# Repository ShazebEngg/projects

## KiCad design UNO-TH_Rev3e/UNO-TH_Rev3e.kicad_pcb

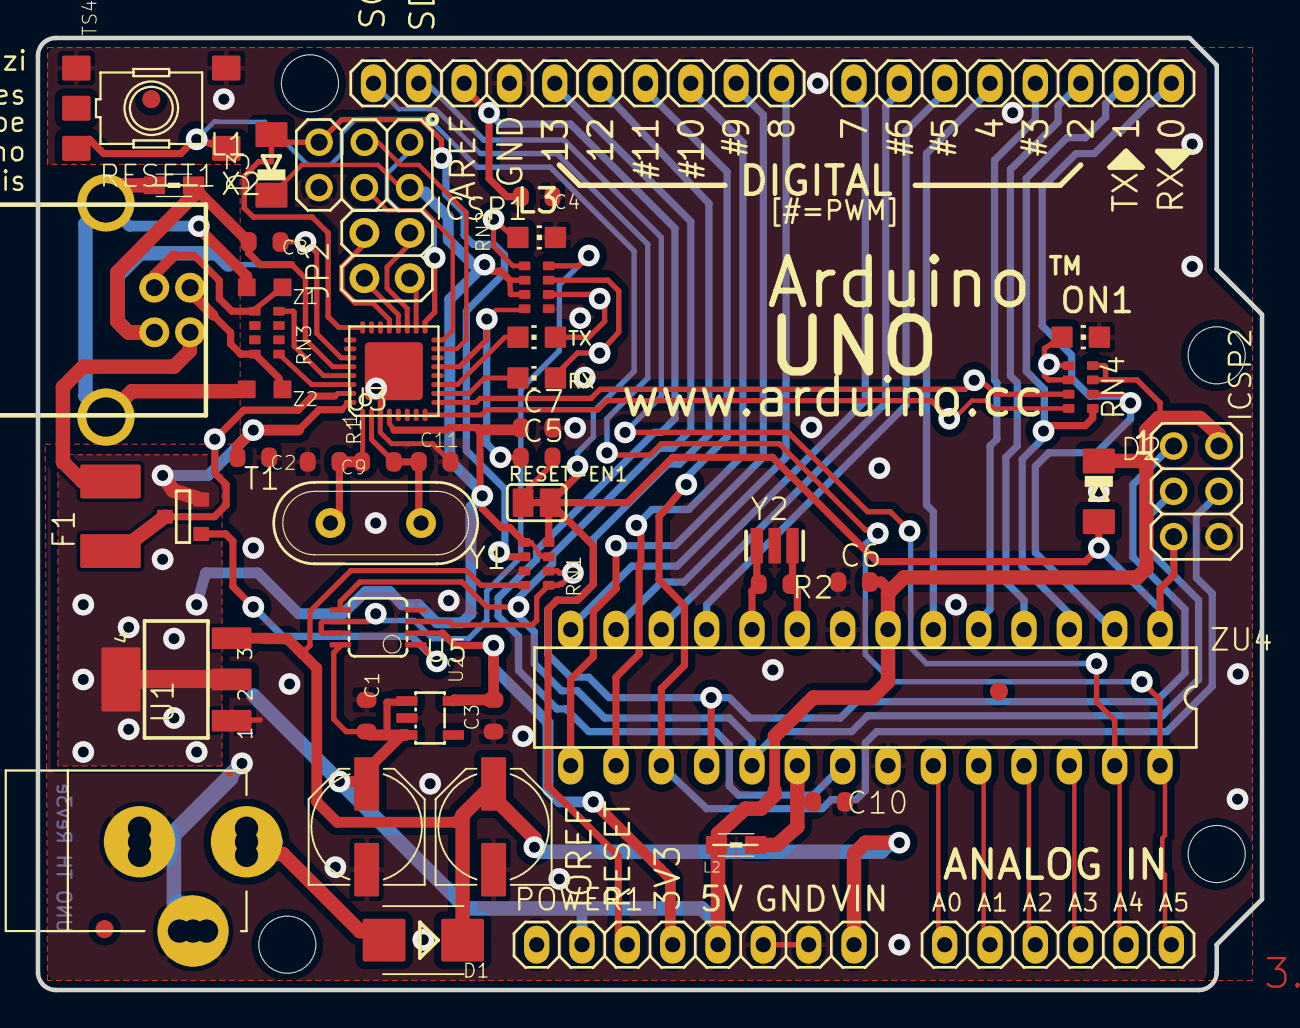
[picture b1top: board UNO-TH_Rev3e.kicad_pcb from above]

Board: 2 copper layers, 68.6 x 53.3 mm, 120 parts (1 on the bottom side), 61 nets.

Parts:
@HOLE0, @HOLE1, @HOLE2, @HOLE3: (no value)
AD1: 6x1F-H8.5; 1X06
C1, C2, C4, C5, C6, C7, C10: 100n; C0603-ROUND
C3, C8: 1u; C0603-ROUND
C9, C11: 22p; C0603-ROUND
D1: M7; SMB
D2, D3: CD1206-S01575; MINIMELF
F1: MF-MSMF050-2 500mA; L1812
FD1, FD2, FD3: FIDUCIALMOUNT; FIDUCIA-MOUNT
FRAME1: DNP; FRAME
GND_TP1, GND_TP2: TP_SP; TP-SP
GROUND1: SJ
ICSP1, ICSP2: 3x2 M; 2X03
IOH1: 10x1F-H8.5; 1X10
IOL1: 8x1F-H8.5; 1X08
JP2: 2x2 M - NM; 2X02
L1: BLM21; 0805
L2: 10uH; 0805
L3: YELLOW; CHIP-LED0805
ON1: GREEN; CHIP-LED0805
ORIGIN1: TP_SP; TP-SP
PC1, PC2: 47u; PANASONIC_D
POWER1: 8x1F-H8.5; 1X08
R1, R2: 1M; R0603-ROUND
RESET1: TS42031-160R-TR-7260; TS42
RESET-EN1: SJ
RN1: 10K; CAY16
RN2, RN4: 1K; CAY16
RN3: 22R; CAY16
RX1: YELLOW; CHIP-LED0805
T1: FDN340P; SOT-23
TP_0, TP_1, TP_2, TP_3, TP_3V3, TP_4, TP_5, TP_5V1, TP_5V2, TP_6, TP_7, TP_8, TP_9, TP_10, TP_11, TP_12, TP_13: TP_SP; TP-SP
TP_A0, TP_A1, TP_A2, TP_A3, TP_A4, TP_A5: TP_SP; TP-SP
TP_AREF1: TP_SP; TP-SP
TP_CMP1: TP_SP; TP-SP
TP_D+1: TP_SP; TP-SP
TP_D-1: TP_SP; TP-SP
TP_DTR1: TP_SP; TP-SP
TP_GATE1: TP_SP; TP-SP
TP_LCMD1: TP_SP; TP-SP
TP_LL1: TP_SP; TP-SP
TP_MISO2: TP_SP; TP-SP
TP_MOSI2: TP_SP; TP-SP
TP_ONL1: TP_SP; TP-SP
TP_PB4, TP_PB5, TP_PB6, TP_PB7: TP_SP; TP-SP
TP_PWRIN1: TP_SP; TP-SP
TP_RESET1, TP_RESET2: TP_SP; TP-SP
TP_RX1: TP_SP; TP-SP
TP_RXL1: TP_SP; TP-SP
TP_SCK2: TP_SP; TP-SP
TP_SCL1: TP_SP; TP-SP
TP_SDA1: TP_SP; TP-SP
TP_TX1: TP_SP; TP-SP
TP_TXL1: TP_SP; TP-SP
TP_UGND1: TP_SP; TP-SP
TP_USBVCC1: TP_SP; TP-SP
TP_USH1: TP_SP; TP-SP
TP_VIN1: TP_SP; TP-SP
TP_VUCAP1: TP_SP; TP-SP
TP_XT1, TP_XT2, TP_XT3, TP_XT4: TP_SP; TP-SP
TP_XUSB1: TP_SP; TP-SP
TX1: YELLOW; CHIP-LED0805
U1: NCP1117ST50T3G; SOT223
U2: LP2985-33DBVR; SOT23-DBV
U3: ATMEGA16U2-MU(R); MLF32
U5: LMV358IDGKR; MSOP08
X1: POWERSUPPLY_DC21MMX; POWERSUPPLY_DC-21MM
X2: USB-B_TH; PN61729
Y1: 16MHz; QS
Y2: CSTCE16M0V53-R0 16MHZ; RESONATOR
Z1, Z2: CG0603MLC-05E; CT_CN0603
ZU4: ATMEGA328P-PU; DIL28-3

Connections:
+5V: C1.2, C2.2, C6.2, C7.1, D2.C, D3.C, ICSP1.2, ICSP2.2, L2.1, PC2.+, POWER1.2, POWER1.5, RN1.3, RN1.5, RN2.2, RN2.3, RN4.3, RN4.4, T1.2, TP_5V1.X, TP_5V2.X, U1.2, U1.4, U2.1, U2.3, U3.4, U3.32, U5.8, ZU4.7
/+3V3: C3.2, POWER1.4, TP_3V3.X, U2.5, U5.2
/AD0: AD1.1, TP_A0.X, ZU4.23
/AD1: AD1.2, TP_A1.X, ZU4.24
/AD2: AD1.3, TP_A2.X, ZU4.25
/AD3: AD1.4, TP_A3.X, ZU4.26
/AD4/SDA: AD1.5, IOH1.9, TP_A4.X, TP_SDA1.X, ZU4.27
/AD5/SCL: AD1.6, IOH1.10, TP_A5.X, TP_SCL1.X, ZU4.28
/AREF: C4.2, IOH1.8, TP_AREF1.X, ZU4.21
/AVCC: C10.2, L2.2, ZU4.20
/CMP: RN1.1, RN1.2, TP_CMP1.X, U5.3
/D+: RN3.5, TP_D+1.X, X2.3, Z1.1
/D-: RN3.8, TP_D-1.X, X2.2, Z2.1
/DTR: C5.1, RN2.4, TP_DTR1.X, U3.13
/GATE_CMD: T1.3, TP_GATE1.X, U5.1
/IO0: IOL1.1, RN4.2, TP_0.X, ZU4.2
/IO1: IOL1.2, RN4.1, TP_1.X, ZU4.3
/IO2: IOL1.3, TP_2.X, ZU4.4
/IO3: IOL1.4, TP_3.X, ZU4.5
/IO4: IOL1.5, TP_4.X, ZU4.6
/IO5: IOL1.6, TP_5.X, ZU4.11
/IO6: IOL1.7, TP_6.X, ZU4.12
/IO7: IOL1.8, TP_7.X, ZU4.13
/IO8: IOH1.1, TP_8.X, ZU4.14
/IO9: IOH1.2, TP_9.X, ZU4.15
/L13: RN2.8, TP_LCMD1.X, U5.6, U5.7
/M8RXD: RN4.7, TP_RX1.X, U3.9
/M8TXD: RN4.8, TP_TX1.X, U3.8
/MISO: ICSP2.1, IOH1.5, TP_12.X, ZU4.18
/MISO2: ICSP1.1, TP_MISO2.X, U3.17
/MOSI: ICSP2.4, IOH1.4, TP_11.X, ZU4.17
/MOSI2: ICSP1.4, TP_MOSI2.X, U3.16
/PB4: JP2.1, TP_PB4.X, U3.18
/PB5: JP2.3, TP_PB5.X, U3.19
/PB6: JP2.2, TP_PB6.X, U3.20
/PB7: JP2.4, TP_PB7.X, U3.21
/PWRIN: D1.A, TP_PWRIN1.X, X1.2
/RD+: RN3.4, U3.29
/RD-: RN3.1, U3.30
/RESET: C5.2, D2.A, ICSP2.5, POWER1.3, RESET1.3, RESET1.4, RESET-EN1.1, RESET-EN1.2, RN1.4, TP_RESET1.X, ZU4.1
/RESET2: D3.A, ICSP1.5, RN1.6, TP_RESET2.X, U3.24
/RXLED: RX1.C, U3.10
/SCK: ICSP2.3, IOH1.6, TP_13.X, U5.5, ZU4.19
/SCK2: ICSP1.3, TP_SCK2.X, U3.15
/SS: IOH1.3, TP_10.X, ZU4.16
/TP_VUCAP: C8.1, TP_VUCAP1.X, U3.27
/TXLED: TX1.C, U3.11
/UGND: C8.2, GROUND1.2, L1.1, TP_UGND1.X, U3.28, X2.4
/USBVCC: F1.1, T1.1, TP_USBVCC1.X, U3.31
/USHIELD: L1.2, TP_USH1.X, X2.P$1, X2.P$2, Z1.2, Z2.2
/VIN: D1.C, PC1.+, POWER1.8, RN1.8, TP_VIN1.X, U1.3
/XT1: C9.1, R1.1, TP_XT3.X, U3.1, Y1.2
/XT2: C11.1, R1.2, TP_XT4.X, U3.2, Y1.1
/XTAL1: R2.1, TP_XT1.X, Y2.3, ZU4.9
/XTAL2: R2.2, TP_XT2.X, Y2.1, ZU4.10
/XUSB: F1.2, TP_XUSB1.X, X2.1
GND: C1.1, C2.1, C3.1, C4.1, C6.1, C7.2, C9.2, C10.1, C11.2, GND_TP1.X, GND_TP2.X, GROUND1.1, ICSP1.6, ICSP2.6, IOH1.7, L3.C, ON1.C, PC1.-, PC2.-, POWER1.6, POWER1.7, RESET1.1, RESET1.2, RN1.7, RN2.5, U1.1, U2.2, U3.3, U3.33, U5.4, X1.1, X1.3, Y2.2, ZU4.8, ZU4.22
unnamed: L3.A, RN2.1, TP_LL1.X
unnamed: ON1.A, RN4.5, RN4.6, TP_ONL1.X
unnamed: RN2.6, TP_TXL1.X, TX1.A
unnamed: RN2.7, RX1.A, TP_RXL1.X

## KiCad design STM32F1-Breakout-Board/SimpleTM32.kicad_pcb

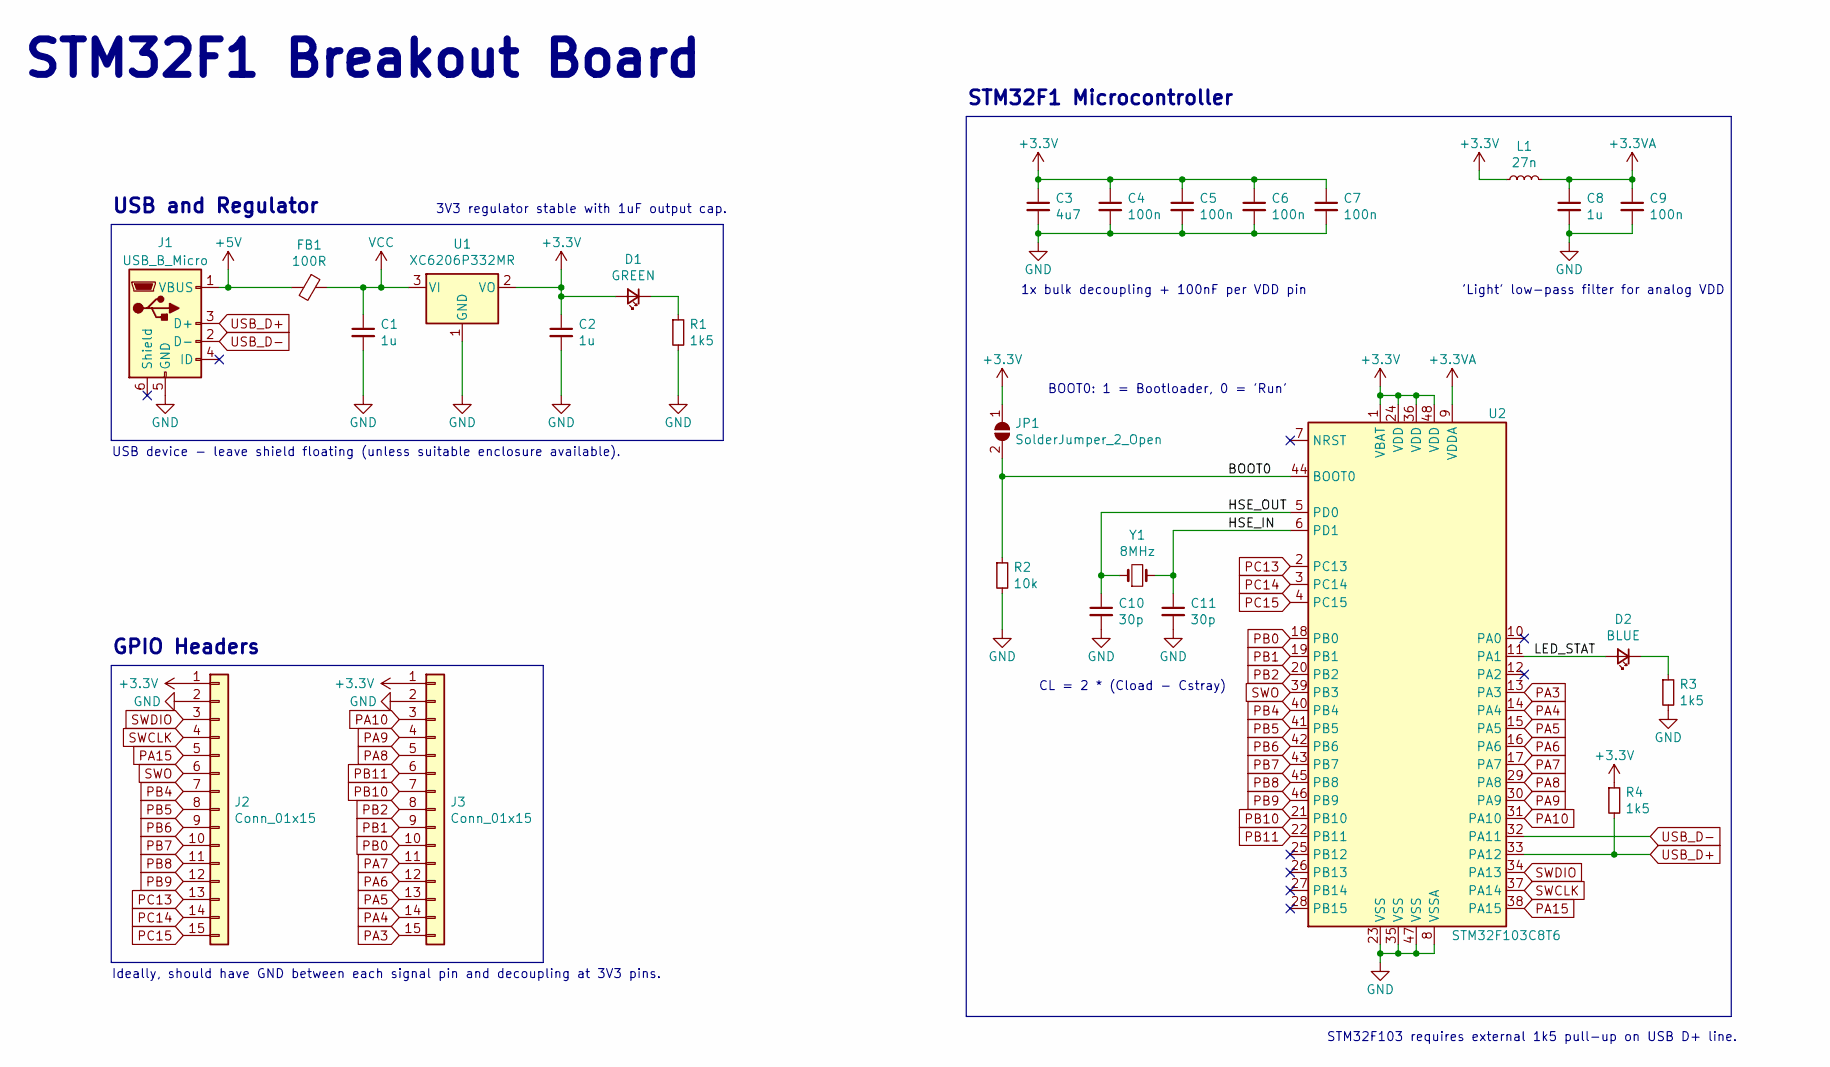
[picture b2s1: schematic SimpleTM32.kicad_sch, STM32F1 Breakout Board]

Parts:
C1, C2: 1u; C_0603_1608Metric; LCSC Part # C15849
C3: 4u7; C_0603_1608Metric; LCSC Part # C19666
C4, C5, C6, C7, C9: 100n; C_0402_1005Metric; LCSC Part # C1525
C8: 1u; C_0402_1005Metric; LCSC Part # C52923
C10, C11: 30p; C_0402_1005Metric; LCSC Part # C1570
D1: GREEN; LED_0603_1608Metric; LCSC Part # C72043
D2: BLUE; LED_0603_1608Metric; LCSC Part # C72041
FB1: 100R; L_0805_2012Metric; LCSC Part # C1015
J1: USB_B_Micro; USB_Micro-B_Wuerth_629105150521
J2, J3: Conn_01x15; PinHeader_1x15_P2.54mm_Vertical
JP1: SolderJumper_2_Open; SolderJumper-2_P1.3mm_Open_Pad1.0x1.5mm
L1: 27n; L_0402_1005Metric; LCSC Part # C18830
R1, R3: 1k5; R_0603_1608Metric; LCSC Part # C22843
R2: 10k; R_0402_1005Metric; LCSC Part # C25744
R4: 1k5; R_0402_1005Metric; LCSC Part # C25867
U1: XC6206P332MR; SOT-23; LCSC Part # C5446
U2: STM32F103C8T6; LQFP-48_7x7mm_P0.5mm; LCSC Part # C8734
Y1: 8MHz; Crystal_SMD_5032-2Pin_5.0x3.2mm; LCSC Part # C115962

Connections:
+3.3VA: C8.1, C9.1, L1.2, U2.9 (VDDA)
+3V3: C2.1, C3.1, C4.1, C5.1, C6.1, C7.1, D1.2 (A), J2.1, J3.1, JP1.1 (A), L1.1, R4.1, U1.2 (VO), U2.1 (VBAT), U2.24 (VDD), U2.36 (VDD), U2.48 (VDD)
+5V: FB1.2, J1.1 (VBUS)
/BOOT0: JP1.2 (B), R2.1, U2.44 (BOOT0)
/HSE_IN: C11.1, U2.6 (PD1), Y1.2
/HSE_OUT: C10.1, U2.5 (PD0), Y1.1
/LED_STAT: D2.2 (A), U2.11 (PA1)
GND: C1.2, C2.2, C3.2, C4.2, C5.2, C6.2, C7.2, C8.2, C9.2, C10.2, C11.2, J1.5 (GND), J2.2, J3.2, R1.2, R2.2, R3.2, U1.1 (GND), U2.8 (VSSA), U2.23 (VSS), U2.35 (VSS), U2.47 (VSS)
unnamed: D1.1 (K), R1.1
unnamed: D2.1 (K), R3.1
PA3: J3.15, U2.13 (PA3)
PA4: J3.14, U2.14 (PA4)
PA5: J3.13, U2.15 (PA5)
PA6: J3.12, U2.16 (PA6)
PA7: J3.11, U2.17 (PA7)
PA8: J3.5, U2.29 (PA8)
PA9: J3.4, U2.30 (PA9)
PA10: J3.3, U2.31 (PA10)
PA15: J2.5, U2.38 (PA15)
PB0: J3.10, U2.18 (PB0)
PB1: J3.9, U2.19 (PB1)
PB2: J3.8, U2.20 (PB2)
PB4: J2.7, U2.40 (PB4)
PB5: J2.8, U2.41 (PB5)
PB6: J2.9, U2.42 (PB6)
PB7: J2.10, U2.43 (PB7)
PB8: J2.11, U2.45 (PB8)
PB9: J2.12, U2.46 (PB9)
PB10: J3.7, U2.21 (PB10)
PB11: J3.6, U2.22 (PB11)
PC13: J2.13, U2.2 (PC13)
PC14: J2.14, U2.3 (PC14)
PC15: J2.15, U2.4 (PC15)
SWCLK: J2.4, U2.37 (PA14)
SWDIO: J2.3, U2.34 (PA13)
SWO: J2.6, U2.39 (PB3)
USB_D+: J1.3 (D+), R4.2, U2.33 (PA12)
USB_D-: J1.2 (D-), U2.32 (PA11)
VCC: C1.1, FB1.1, U1.3 (VI)

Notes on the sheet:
BOOT0: 1 = Bootloader, 0 = 'Run'
STM32F1 Breakout Board
3V3 regulator stable with 1uF output cap.
Ideally, should have GND between each signal pin and decoupling at 3V3 pins.
USB device - leave shield floating (unless suitable enclosure available).
1x bulk decoupling + 100nF per VDD pin
GPIO Headers
CL = 2 * (Cload - Cstray)
STM32F1 Microcontroller
'Light' low-pass filter for analog VDD
USB and Regulator
STM32F103 requires external 1k5 pull-up on USB D+ line.

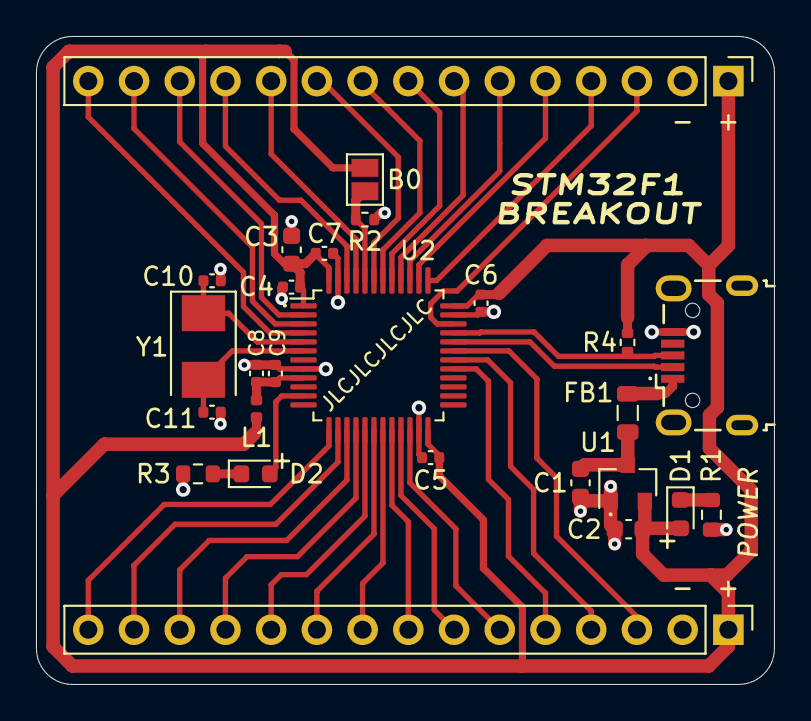
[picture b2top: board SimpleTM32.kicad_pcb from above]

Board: 2 copper layers, 41.0 x 36.0 mm, 26 parts (0 on the bottom side), 39 nets.

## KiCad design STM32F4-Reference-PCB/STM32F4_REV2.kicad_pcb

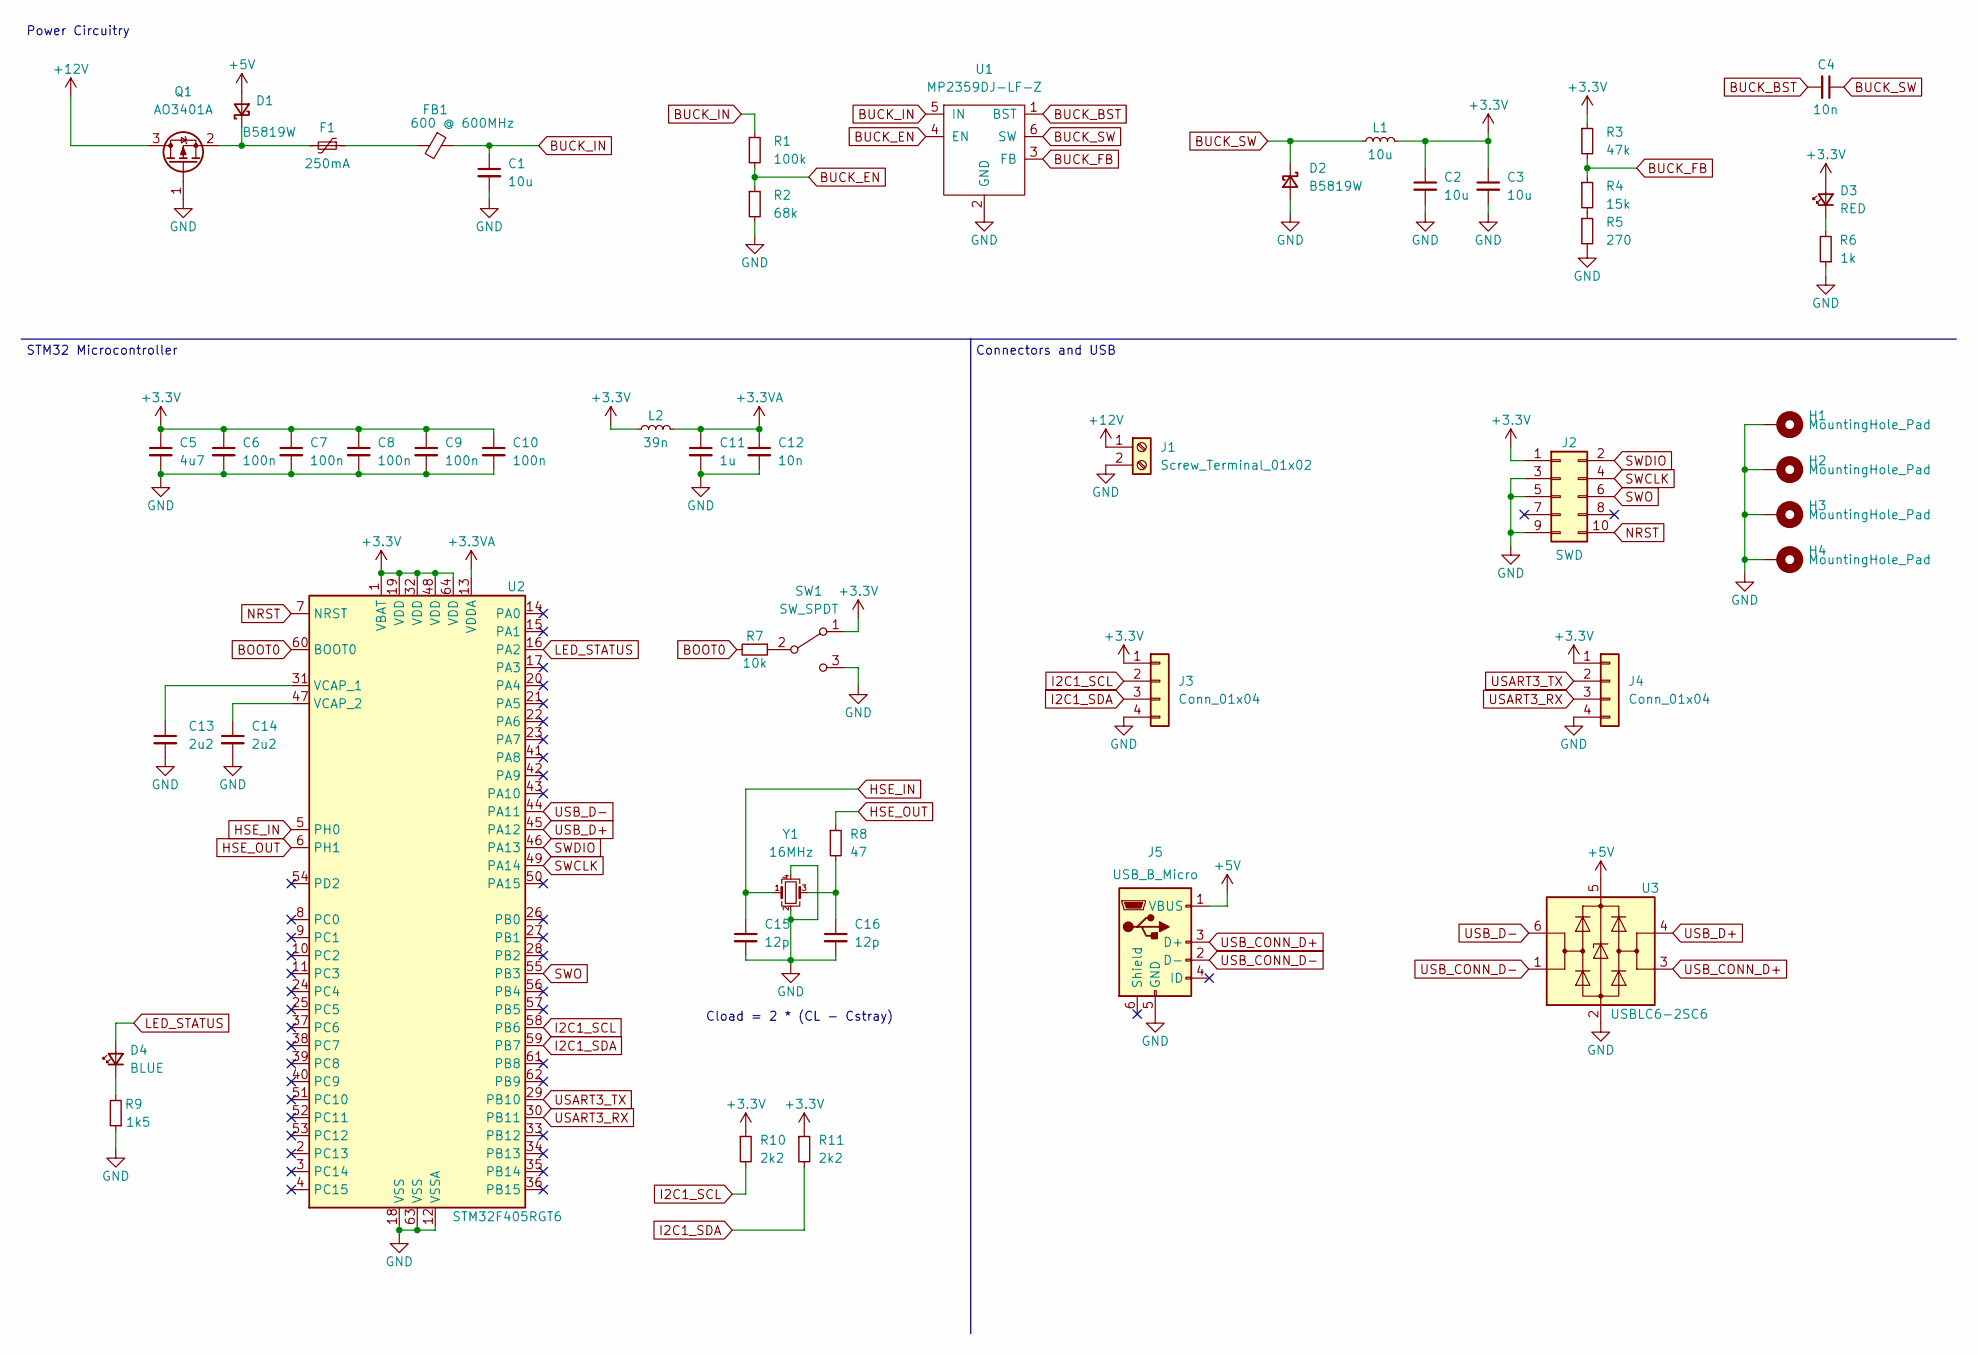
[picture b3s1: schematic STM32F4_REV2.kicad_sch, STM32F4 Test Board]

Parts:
C1, C2, C3: 10u; C_1206_3216Metric; LCSC Part # C13585
C4: 10n; C_0603_1608Metric; LCSC Part # C57112
C5: 4u7; C_0603_1608Metric; LCSC Part # C19666
C6, C7, C8, C9, C10: 100n; C_0402_1005Metric; LCSC Part # C1525
C11: 1u; C_0402_1005Metric; LCSC Part # C52923
C12: 10n; C_0402_1005Metric; LCSC Part # C15195
C13, C14: 2u2; C_0603_1608Metric; LCSC Part # C23630
C15, C16: 12p; C_0402_1005Metric; LCSC Part # C1547
D1, D2: B5819W; D_SOD-123; LCSC Part # C8598
D3: RED; LED_0603_1608Metric; LCSC Part # C2286
D4: BLUE; LED_0603_1608Metric; LCSC Part # C72041
F1: 250mA; Fuse_1206_3216Metric; LCSC Part # C369159
FB1: 600 @ 600MHz; L_0805_2012Metric; LCSC Part # C1017
H1, H2, H3, H4: MountingHole_Pad; MountingHole_4.3mm_M4_Pad_Via
J1: Screw_Terminal_01x02; TerminalBlock_Phoenix_PT-1,5-2-3.5-H_1x02_P3.50mm_Horizontal
J2: SWD; PinHeader_2x05_P1.27mm_Vertical_SMD
J3, J4: Conn_01x04; Molex_PicoBlade_53048-0410_1x04_P1.25mm_Horizontal
J5: USB_B_Micro; USB_MICRO_B_101181930001LF
L1: 10u; L_Sunlord_MWSA0518_5.4x5.2mm; LCSC Part # C139506
L2: 39n; L_0402_1005Metric; LCSC Part # C26443
Q1: AO3401A; SOT-23; LCSC Part # C15127
R1: 100k; R_0603_1608Metric; LCSC Part # C25803
R2: 68k; R_0603_1608Metric; LCSC Part # C23231
R3: 47k; R_0603_1608Metric; LCSC Part # C25819
R4: 15k; R_0603_1608Metric; LCSC Part # C22809
R5: 270; R_0603_1608Metric; LCSC Part # C22966
R6: 1k; R_0603_1608Metric; LCSC Part # C21190
R7: 10k; R_0402_1005Metric; LCSC Part # C25744
R8: 47; R_0402_1005Metric; LCSC Part # C25118
R9: 1k5; R_0603_1608Metric; LCSC Part # C22843
R10, R11: 2k2; R_0402_1005Metric; LCSC Part # C25879
SW1: SW_SPDT; SW_SPDT_PCM12
U1: MP2359DJ-LF-Z; SOT-23-6; LCSC Part # C14259
U2: STM32F405RGT6; LQFP-64_10x10mm_P0.5mm; LCSC Part # C15742
U3: USBLC6-2SC6; SOT-23-6; LCSC Part # C7519
Y1: 16MHz; Crystal_SMD_3225-4Pin_3.2x2.5mm; LCSC Part # C13738

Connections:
+3.3VA: C11.1, C12.1, L2.2, U2.13 (VDDA)
+3V3: C2.1, C3.1, C5.1, C6.1, C7.1, C8.1, C9.1, C10.1, D3.2 (A), J2.1, J3.1, J4.1, L1.2, L2.1, R3.1, R10.1, R11.1, SW1.1 (A), U2.1 (VBAT), U2.19 (VDD), U2.32 (VDD), U2.48 (VDD), U2.64 (VDD)
+5V: D1.2 (A), J5.1 (VBUS), U3.5 (VBUS)
+12V: J1.1, Q1.3 (D)
BOOT0: R7.2, U2.60 (BOOT0)
BUCK_BST: C4.2, U1.1 (BST)
BUCK_EN: R1.2, R2.1, U1.4 (EN)
BUCK_FB: R3.2, R4.1, U1.3 (FB)
BUCK_IN: C1.1, FB1.1, R1.1, U1.5 (IN)
BUCK_SW: C4.1, D2.1 (K), L1.1, U1.6 (SW)
GND: C1.2, C2.2, C3.2, C5.2, C6.2, C7.2, C8.2, C9.2, C10.2, C11.2, C12.2, C13.2, C14.2, C15.2, C16.2, D2.2 (A), H1.1, H2.1, H3.1, H4.1, J1.2, J2.3, J2.5, J2.9, J3.4, J4.4, J5.5 (GND), Q1.1 (G), R2.2, R5.2, R6.1, R9.1, SW1.3 (C), U1.2 (GND), U2.12 (VSSA), U2.18 (VSS), U2.63 (VSS), U3.2 (GND), Y1.2, Y1.4
HSE_IN: C15.1, U2.5 (PH0), Y1.1
HSE_OUT: R8.1, U2.6 (PH1)
I2C1_SCL: J3.2, R10.2, U2.58 (PB6)
I2C1_SDA: J3.3, R11.2, U2.59 (PB7)
LED_STATUS: D4.2 (A), U2.16 (PA2)
NRST: J2.10, U2.7 (NRST)
unnamed: C13.1, U2.31 (VCAP_1)
unnamed: C14.1, U2.47 (VCAP_2)
unnamed: C16.1, R8.2, Y1.3
unnamed: D1.1 (K), F1.2, Q1.2 (S)
unnamed: D3.1 (K), R6.2
unnamed: D4.1 (K), R9.2
unnamed: F1.1, FB1.2
unnamed: R4.2, R5.1
unnamed: R7.1, SW1.2 (B)
SWCLK: J2.4, U2.49 (PA14)
SWDIO: J2.2, U2.46 (PA13)
SWO: J2.6, U2.55 (PB3)
USART3_RX: J4.3, U2.30 (PB11)
USART3_TX: J4.2, U2.29 (PB10)
USB_CONN_D+: J5.3 (D+), U3.3 (I/O2)
USB_CONN_D-: J5.2 (D-), U3.1 (I/O1)
USB_D+: U2.45 (PA12), U3.4 (I/O2)
USB_D-: U2.44 (PA11), U3.6 (I/O1)

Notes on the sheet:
Cload = 2 * (CL - Cstray)
STM32 Microcontroller
Power Circuitry
Connectors and USB

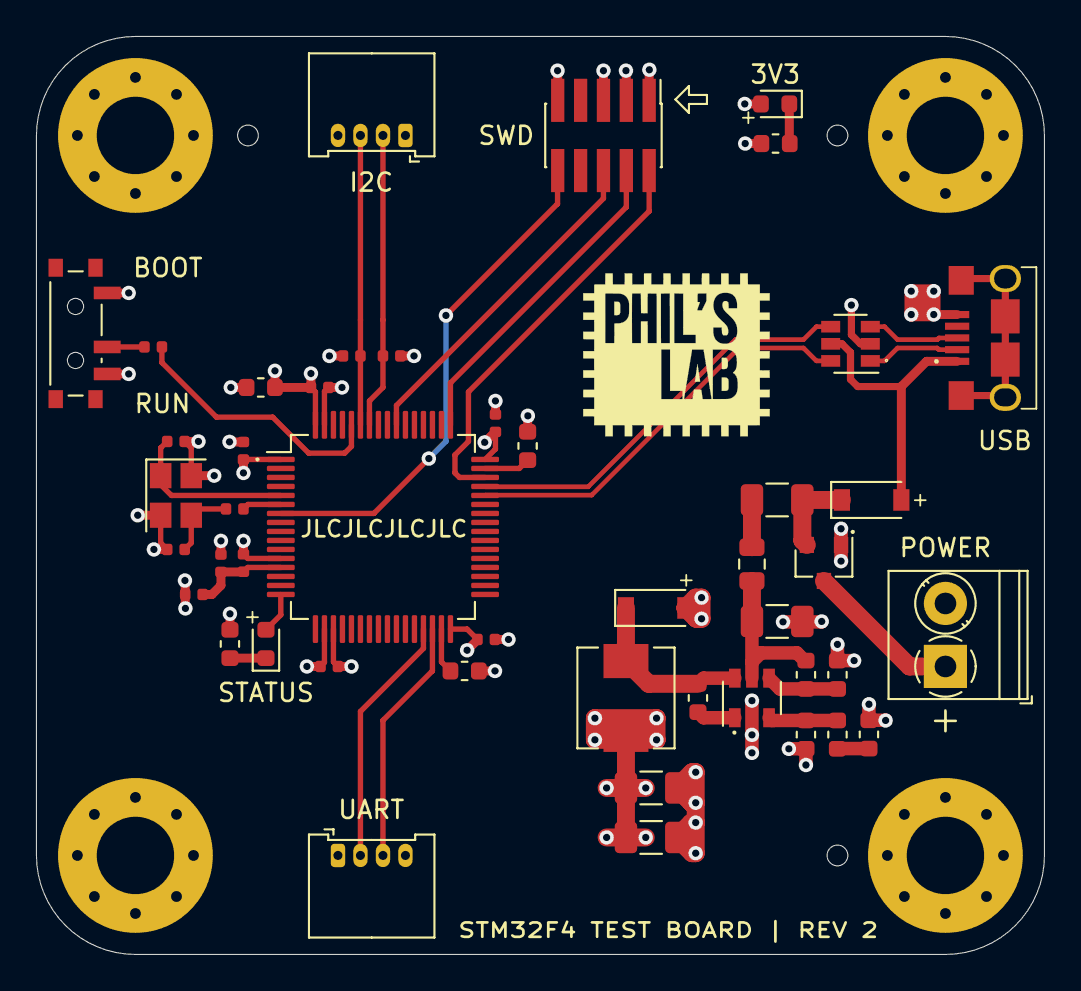
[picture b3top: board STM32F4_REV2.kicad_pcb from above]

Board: 4 copper layers, 56.0 x 51.0 mm, 50 parts (0 on the bottom side), 35 nets.

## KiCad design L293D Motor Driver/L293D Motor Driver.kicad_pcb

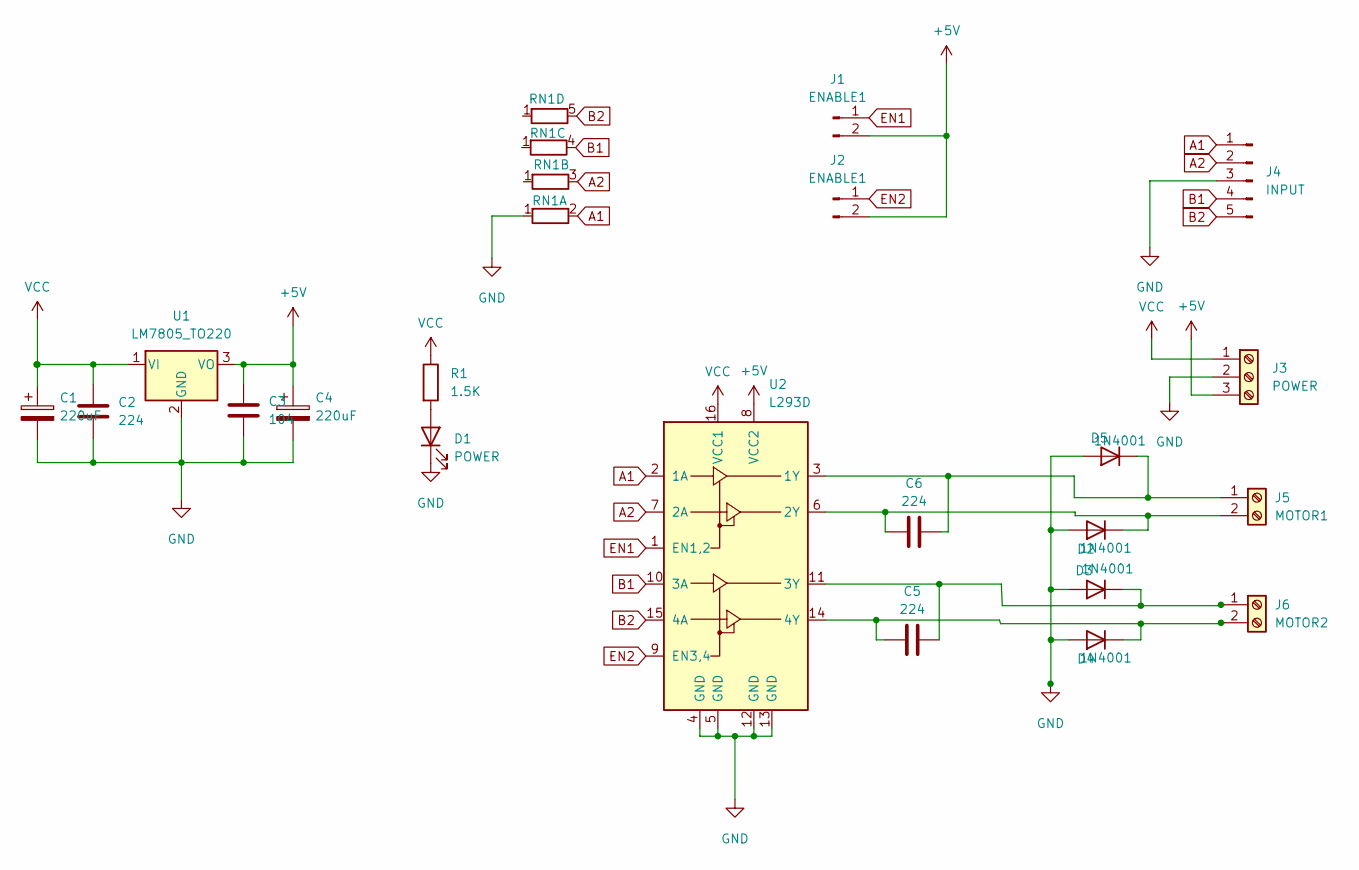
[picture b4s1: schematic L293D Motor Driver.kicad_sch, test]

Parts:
C1, C4: 220uF; CP_Radial_D10.0mm_P5.00mm
C2, C5, C6: 224; C_Disc_D9.0mm_W2.5mm_P5.00mm
C3: 104; C_Disc_D5.0mm_W2.5mm_P2.50mm
D1: POWER; LED_D3.0mm
D2, D3, D4, D5: 1N4001; D_DO-41_SOD81_P10.16mm_Horizontal
J1, J2: ENABLE1; PinHeader_1x02_P2.54mm_Vertical
J3: POWER; TerminalBlock_Phoenix_MKDS-1,5-3-5.08_1x03_P5.08mm_Horizont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
J4: INPUT; PinHeader_1x05_P2.54mm_Vertical
J5: MOTOR1; TerminalBlock_Phoenix_MKDS-1,5-2-5.08_1x02_P5.08mm_Horizont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
J6: MOTOR2; TerminalBlock_Phoenix_MKDS-1,5-2-5.08_1x02_P5.08mm_Horizont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
R1: 1.5K; R_Axial_DIN0207_L6.3mm_D2.5mm_P10.16mm_Horizontal
RN1: A103J; R_Array_SIP5
U1: LM7805_TO220; TO-220-3_Vertical
U2: L293D; DIP-16_W7.62mm

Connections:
+5V: C3.1, C4.1, J1.2, J2.2, J3.3, U1.3 (VO), U2.8 (VCC2)
A1: J4.1, RN1.2 (R1.2), U2.2 (1A)
A2: J4.2, RN1.3 (R2.2), U2.7 (2A)
B1: J4.4, RN1.4 (R3.2), U2.10 (3A)
B2: J4.5, RN1.5 (R4.2), U2.15 (4A)
EN1: J1.1, U2.1 (EN1,2)
EN2: J2.1, U2.9 (EN3,4)
GND: C1.2, C2.2, C3.2, C4.2, D1.1 (K), D2.2 (A), D3.2 (A), D4.2 (A), D5.2 (A), J3.2, J4.3, RN1.1 (R1.1), U1.2 (GND), U2.4 (GND), U2.5 (GND), U2.12 (GND), U2.13 (GND)
unnamed: C5.1, D4.1 (K), J6.2, U2.14 (4Y)
unnamed: C5.2, D3.1 (K), J6.1, U2.11 (3Y)
unnamed: C6.1, D5.1 (K), J5.1, U2.3 (1Y)
unnamed: C6.2, D2.1 (K), J5.2, U2.6 (2Y)
unnamed: D1.2 (A), R1.2
VCC: C1.1, C2.1, J3.1, R1.1, U1.1 (VI), U2.16 (VCC1)

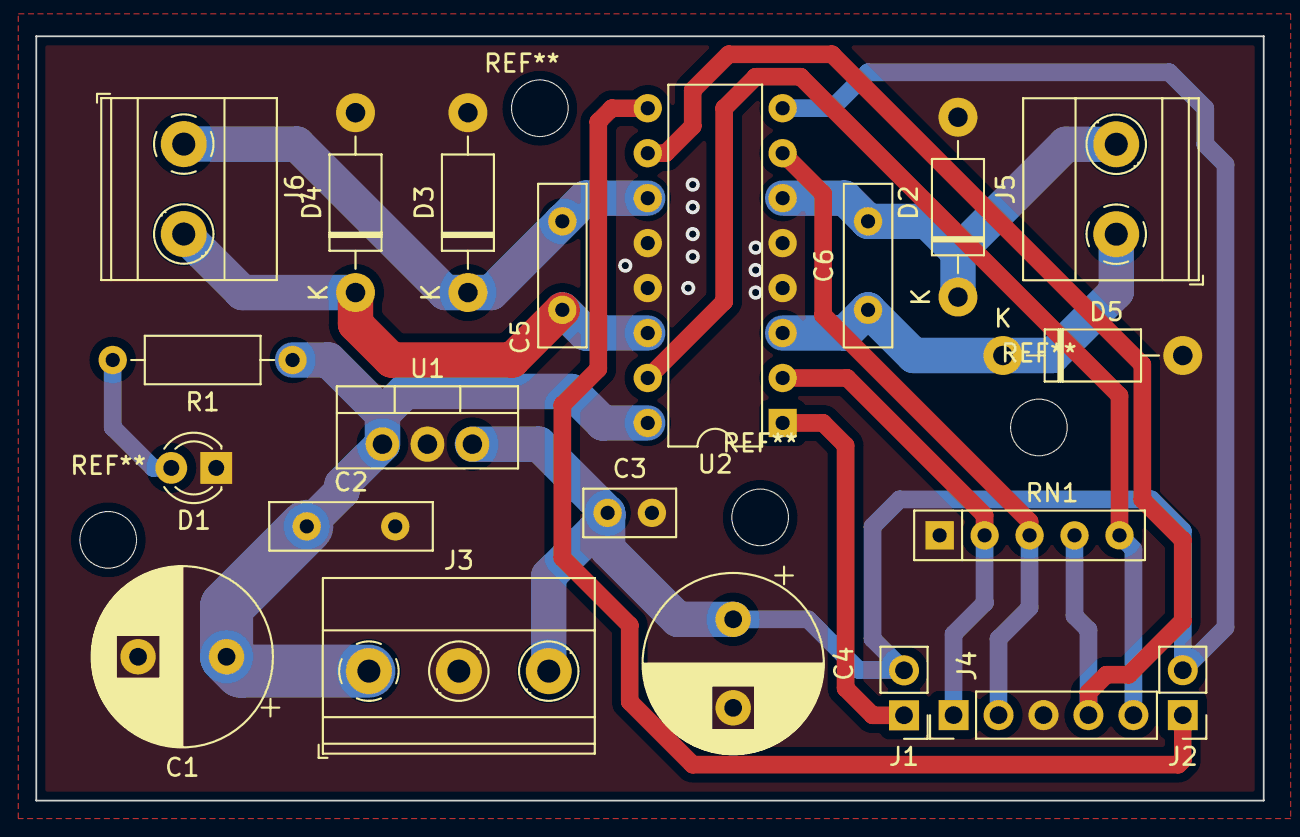
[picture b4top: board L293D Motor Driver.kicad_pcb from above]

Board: 2 copper layers, 69.3 x 43.2 mm, 21 parts (0 on the bottom side), 14 nets.

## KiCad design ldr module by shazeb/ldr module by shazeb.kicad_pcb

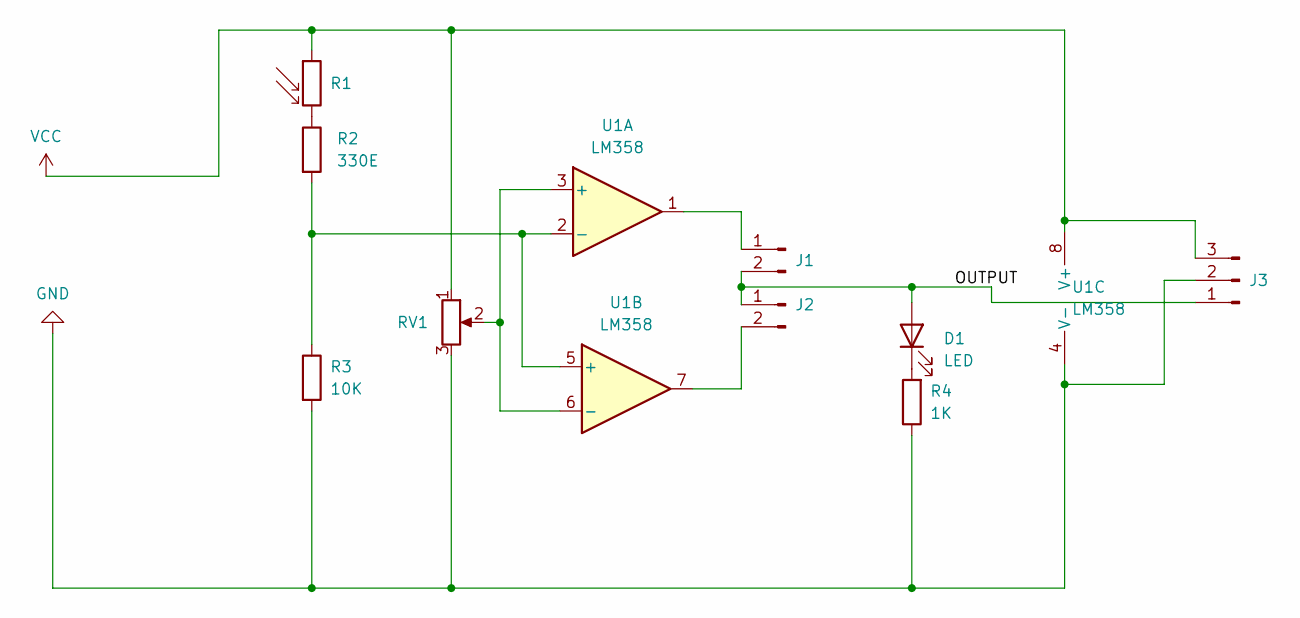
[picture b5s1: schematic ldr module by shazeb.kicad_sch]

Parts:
D1: LED; LED_D3.0mm_Clear
J1, J2: Conn_01x02_Male; PinHeader_1x02_P2.54mm_Vertical
J3: Conn_01x03_Male; PinHeader_1x03_P2.54mm_Vertical
R1: R_Photo; R_LDR_4.9x4.2mm_P2.54mm_Vertical
R2: 330E; R_Axial_DIN0411_L9.9mm_D3.6mm_P12.70mm_Horizontal
R3: 10K; R_Axial_DIN0411_L9.9mm_D3.6mm_P12.70mm_Horizontal
R4: 1K; R_Axial_DIN0411_L9.9mm_D3.6mm_P12.70mm_Horizontal
RV1: 10K; Potentiometer_Runtron_RM-065_Vertical
U1: LM358; DIP-8_W7.62mm

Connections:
/OUTPUT: D1.2 (A), J1.2, J2.1, J3.1
GND: J3.2, R3.2, R4.1, RV1.3, U1.4 (V-)
unnamed: D1.1 (K), R4.2
unnamed: J1.1, U1.1
unnamed: J2.2, U1.7
unnamed: R1.2, R2.1
unnamed: R2.2, R3.1, U1.2 (-), U1.5 (+)
unnamed: RV1.2, U1.3 (+), U1.6 (-)
VCC: J3.3, R1.1, RV1.1, U1.8 (V+)

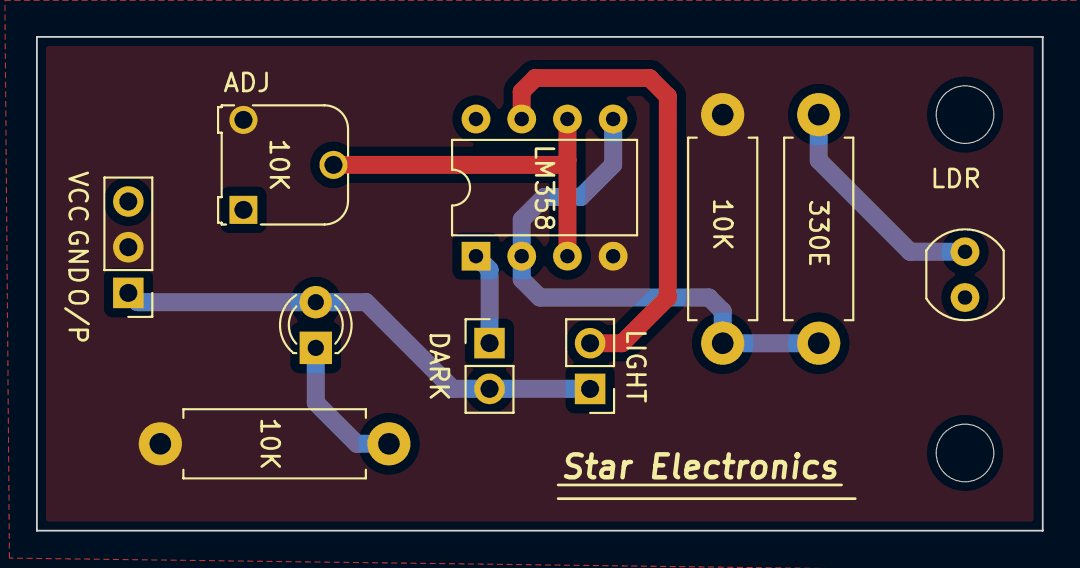
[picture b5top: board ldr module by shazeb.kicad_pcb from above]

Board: 2 copper layers, 55.9 x 27.4 mm, 10 parts (0 on the bottom side), 9 nets.

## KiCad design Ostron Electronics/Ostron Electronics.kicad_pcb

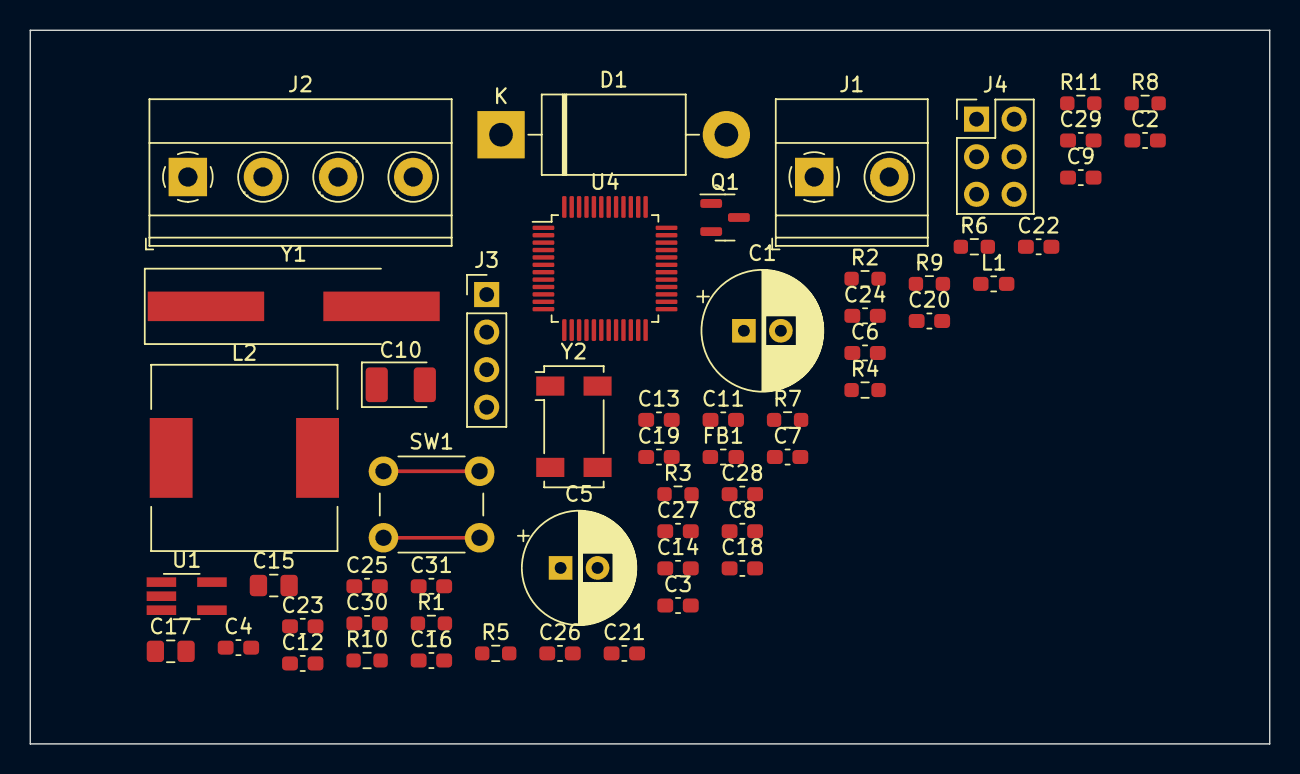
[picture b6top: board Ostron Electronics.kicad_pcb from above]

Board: 2 copper layers, 83.8 x 48.3 mm, 56 parts (0 on the bottom side), 33 nets.

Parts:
C1: 220u; CP_Radial_D8.0mm_P2.50mm
C2, C4, C7, C8, C9, C11, C16, C19, C22: 100n; C_0603_1608Metric_Pad1.08x0.95mm_HandSolder
C3, C24: 1u; C_0603_1608Metric_Pad1.08x0.95mm_HandSolder
C5: 100u; CP_Radial_D7.5mm_P2.50mm
C6: 4u7; C_0603_1608Metric_Pad1.08x0.95mm_HandSolder
C10: 100uF; CP_EIA-3528-21_Kemet-B_Pad1.50x2.35mm_HandSolder
C12, C18, C26, C27, C28, C29: 33p; C_0603_1608Metric_Pad1.08x0.95mm_HandSolder
C13, C20, C21: 10p; C_0603_1608Metric_Pad1.08x0.95mm_HandSolder
C14: 4.7u; C_0603_1608Metric_Pad1.08x0.95mm_HandSolder
C15: 22u; C_0805_2012Metric_Pad1.18x1.45mm_HandSolder
C17: 10u; C_0805_2012Metric_Pad1.18x1.45mm_HandSolder
C23, C25, C30, C31: 20p; C_0603_1608Metric_Pad1.08x0.95mm_HandSolder
D1: D_Schottky; D_DO-201AD_P15.24mm_Horizontal
FB1: 100R; L_0603_1608Metric_Pad1.05x0.95mm_HandSolder
J1: Battery; TerminalBlock_Phoenix_MKDS-1,5-2-5.08_1x02_P5.08mm_Horizont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
J2: PIEZOMETER; TerminalBlock_Phoenix_MKDS-1,5-4-5.08_1x04_P5.08mm_Horizont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
J3: SWD; PinHeader_1x04_P2.54mm_Vertical
J4: BOOT; PinHeader_2x03_P2.54mm_Vertical
L1: 27n; L_0603_1608Metric_Pad1.05x0.95mm_HandSolder
L2: 22uH; L_12x12mm_H6mm
Q1: DTC114E; SOT-23
R1: 5.6k; R_0603_1608Metric_Pad0.98x0.95mm_HandSolder
R2: 1k; R_0603_1608Metric_Pad0.98x0.95mm_HandSolder
R3: 1K; R_0603_1608Metric_Pad0.98x0.95mm_HandSolder
R4: 0E; R_0603_1608Metric_Pad0.98x0.95mm_HandSolder
R5, R6: 100K; R_0603_1608Metric_Pad0.98x0.95mm_HandSolder
R7: 10k; R_0603_1608Metric_Pad0.98x0.95mm_HandSolder
R8, R9, R11: 22R; R_0603_1608Metric_Pad0.98x0.95mm_HandSolder
R10: 1M; R_0603_1608Metric_Pad0.98x0.95mm_HandSolder
SW1: RESET; SW_PUSH_6mm_H4.3mm
U1: TPS76933; TSOT-23-5_HandSoldering
U4: STM32F103C8T6; LQFP-48_7x7mm_P0.5mm
Y1: 8MHz; Crystal_SMD_HC49-SD_HandSoldering
Y2: 32.768KHz; Crystal_SMD_Abracon_ABS25-4Pin_8.0x3.8mm

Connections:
+3.3VA: C3.1, C4.1, L1.2, U4.9 (VDDA)
+3V3: C6.1, C7.1, C8.1, C9.1, C16.1, C17.1, C19.1, J3.1, J4.1, J4.2, L1.1, R7.1, U1.5 (OUT), U4.36 (VDD)
+4V: C5.1, C10.1, C11.1, C12.1, C13.1, C14.1, D1.1 (K), R1.1
+BATT: C1.1, C2.1, FB1.2, J1.1, L2.1
Boot0: R5.2, U4.44 (BOOT0)
Boot1: R6.1, U4.20 (PB2)
COIL+: J2.1, U4.10 (PA0)
COIL-: J2.2, U4.17 (PA7)
GND: C1.2, C2.2, C3.2, C4.2, C5.2, C6.2, C7.2, C8.2, C9.2, C10.2, C11.2, C12.2, C13.2, C14.2, C15.2, C16.2, C17.2, C18.2, C19.2, C20.2, C21.2, C24.2, C30.2, C31.2, J1.2, J2.4, J3.4, J4.5, J4.6, Q1.2 (E), R2.2, R3.1, SW1.1, U1.2 (GND), U1.3 (~EN), U4.8 (VSSA), U4.23 (VSS), U4.35 (VSS), U4.47 (VSS)
unnamed: C15.1, FB1.1, U1.1 (IN)
unnamed: C20.1, R4.1
unnamed: C21.1, R4.2
unnamed: C23.2, C25.2
unnamed: C26.1, R11.1
unnamed: C27.1, R9.2
unnamed: C28.1, R8.2
unnamed: D1.2 (A), L2.2
unnamed: J4.3, R5.1
unnamed: J4.4, R6.2
unnamed: R1.2, R2.1
unnamed: U4.24 (VDD), U4.48 (VDD)
OSCIN: C23.1, R10.1, U4.5 (PD0), Y1.1
OSCOUT: C25.1, R10.2, U4.6 (PD1), Y1.2
PC14: C30.1, U4.3 (PC14), Y2.1
PC15: C31.1, U4.4 (PC15), Y2.4
RESET: C24.1, R7.2, SW1.2, U4.7 (NRST)
RST: C18.1, Q1.1 (B), U4.41 (PB5)
SIM_GND: C22.1, C26.2, C27.2, C28.2, C29.2
SIM_VDD: C22.2, C29.1
SWDCLK: J3.3, U4.37 (PA14)
SWDIO: J3.2, U4.34 (PA13)
THERMISTER_IN: R3.2, U4.11 (PA1)
THERMISTER_OUT: J2.3, U4.27 (PB14)
